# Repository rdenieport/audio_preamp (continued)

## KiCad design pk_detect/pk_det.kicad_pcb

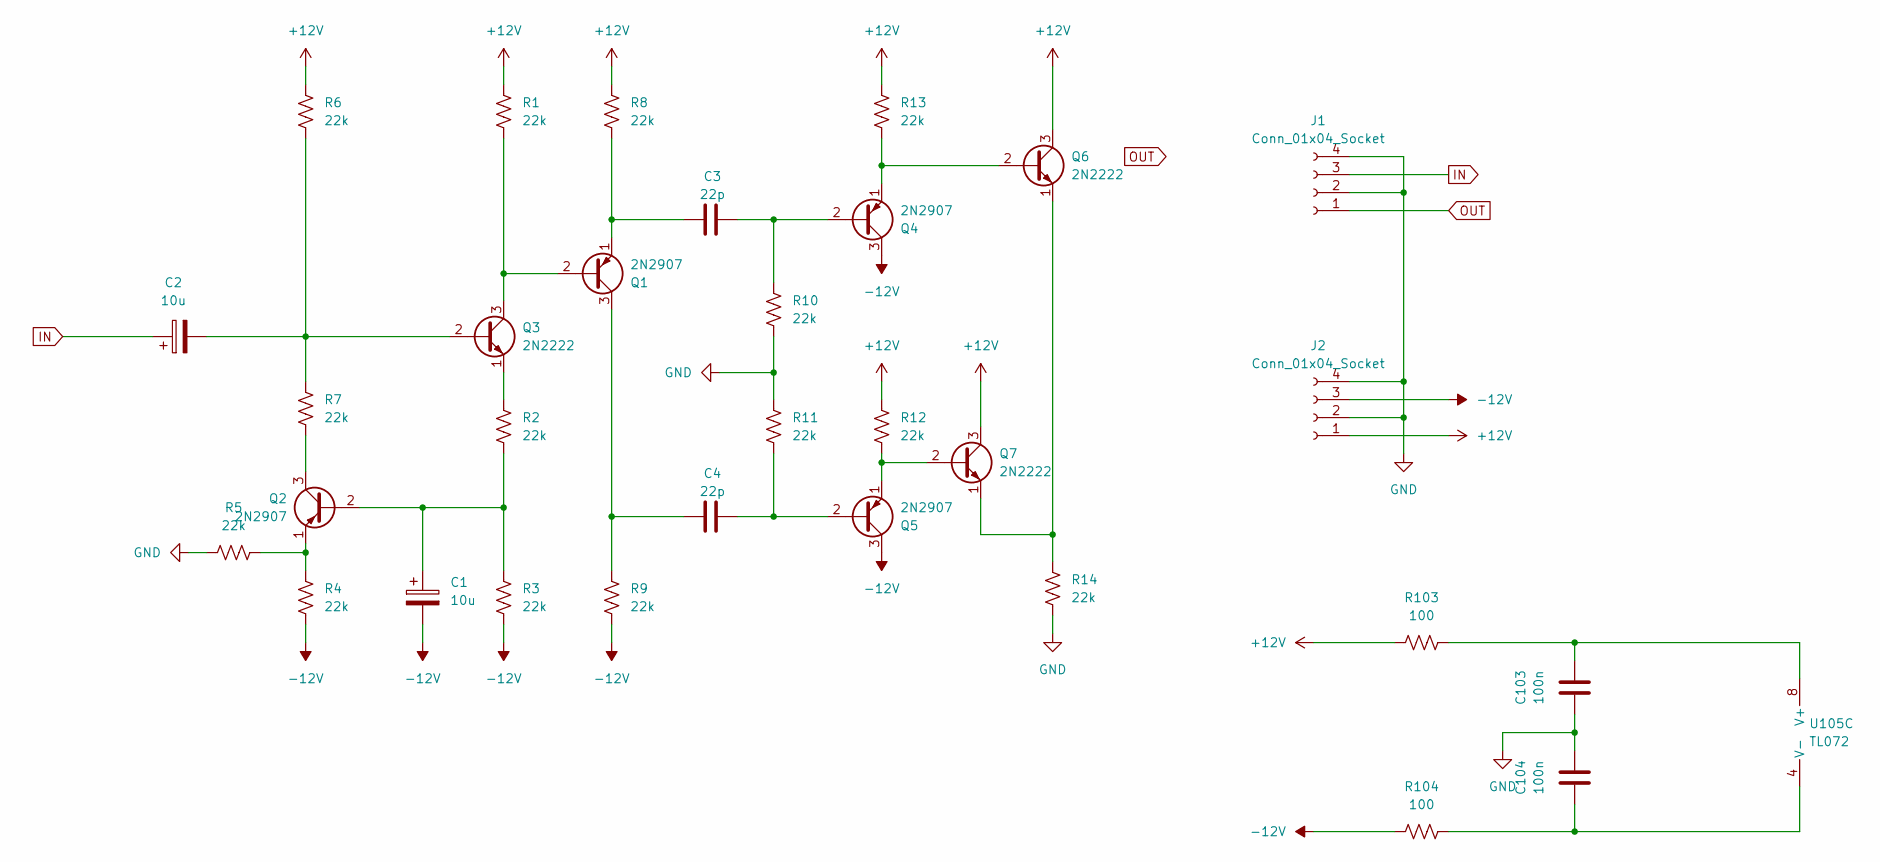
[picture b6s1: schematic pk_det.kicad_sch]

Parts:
C1, C2: 10u; CP_Radial_D6.3mm_P2.50mm
C3, C4: 22p; C_Disc_D4.3mm_W1.9mm_P5.00mm
C103, C104: 100n; C_Disc_D4.3mm_W1.9mm_P5.00mm
J1, J2: Conn_01x04_Socket; Molex_KK-254_AE-6410-04A_1x04_P2.54mm_Vertical
Q1, Q2, Q4, Q5: 2N2907; TO-46-3
Q3, Q6, Q7: 2N2222; TO-46-3
R1, R2, R3, R4, R5, R6, R7, R8, R9, R10, R11, R12, R13, R14: 22k; R_Axial_DIN0207_L6.3mm_D2.5mm_P10.16mm_Horizontal
R103, R104: 100; R_Axial_DIN0207_L6.3mm_D2.5mm_P10.16mm_Horizontal
U105: TL072; DIP-8_W7.62mm_LongPads

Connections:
+12V: J2.1, Q6.3 (C), Q7.3 (C), R1.1, R6.1, R8.1, R12.1, R13.1, R103.1
-12V: C1.2, J2.3, Q4.3 (C), Q5.3 (C), R3.2, R4.2, R9.2, R104.1
GND: C103.1, C104.2, J1.2, J1.4, J2.2, J2.4, R5.2, R10.2, R11.1, R14.2
IN: C2.1, J1.3
unnamed: Q1.2 (B), Q3.3 (C), R1.2
unnamed: C4.1, Q1.3 (C), R9.1
unnamed: C3.1, Q1.1 (E), R8.2
unnamed: C1.1, Q2.2 (B), R2.2, R3.1
unnamed: Q2.3 (C), R7.2
unnamed: Q2.1 (E), R4.1, R5.1
unnamed: C2.2, Q3.2 (B), R6.2, R7.1
unnamed: Q3.1 (E), R2.1
unnamed: C3.2, Q4.2 (B), R10.1
unnamed: Q4.1 (E), Q6.2 (B), R13.2
unnamed: C4.2, Q5.2 (B), R11.2
unnamed: Q5.1 (E), Q7.2 (B), R12.2
unnamed: Q6.1 (E), Q7.1 (E), R14.1
unnamed: C103.2, R103.2, U105.8 (V+)
unnamed: C104.1, R104.2, U105.4 (V-)
OUT: J1.1

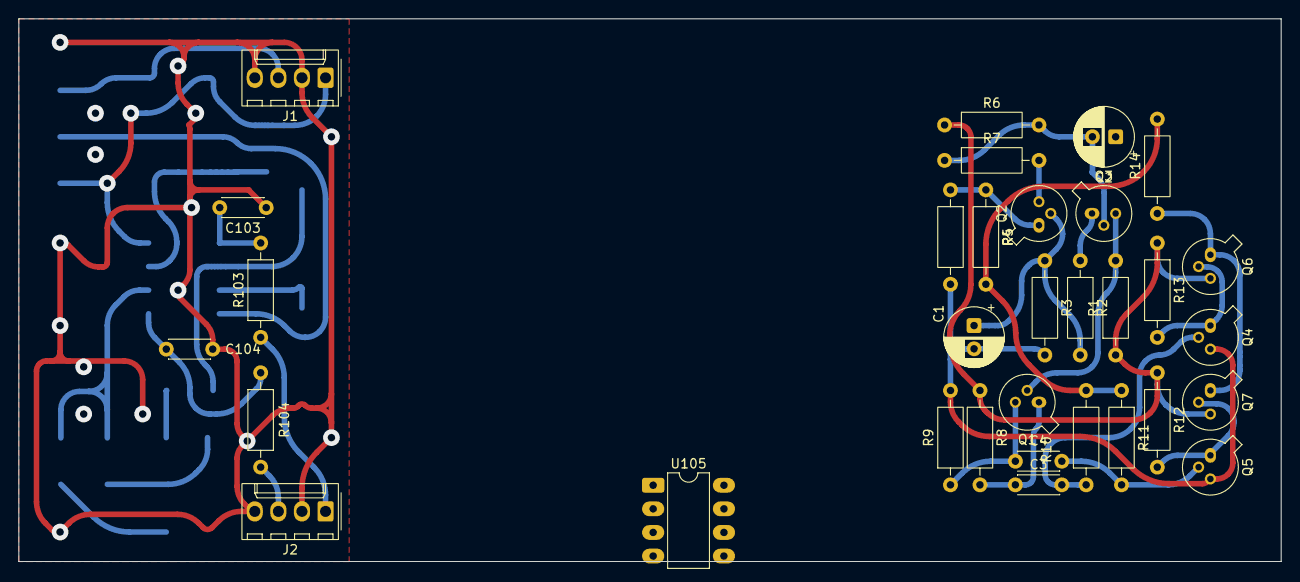
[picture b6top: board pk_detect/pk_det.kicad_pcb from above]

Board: 2 copper layers, 135.9 x 58.4 mm, 32 parts (0 on the bottom side), 19 nets.

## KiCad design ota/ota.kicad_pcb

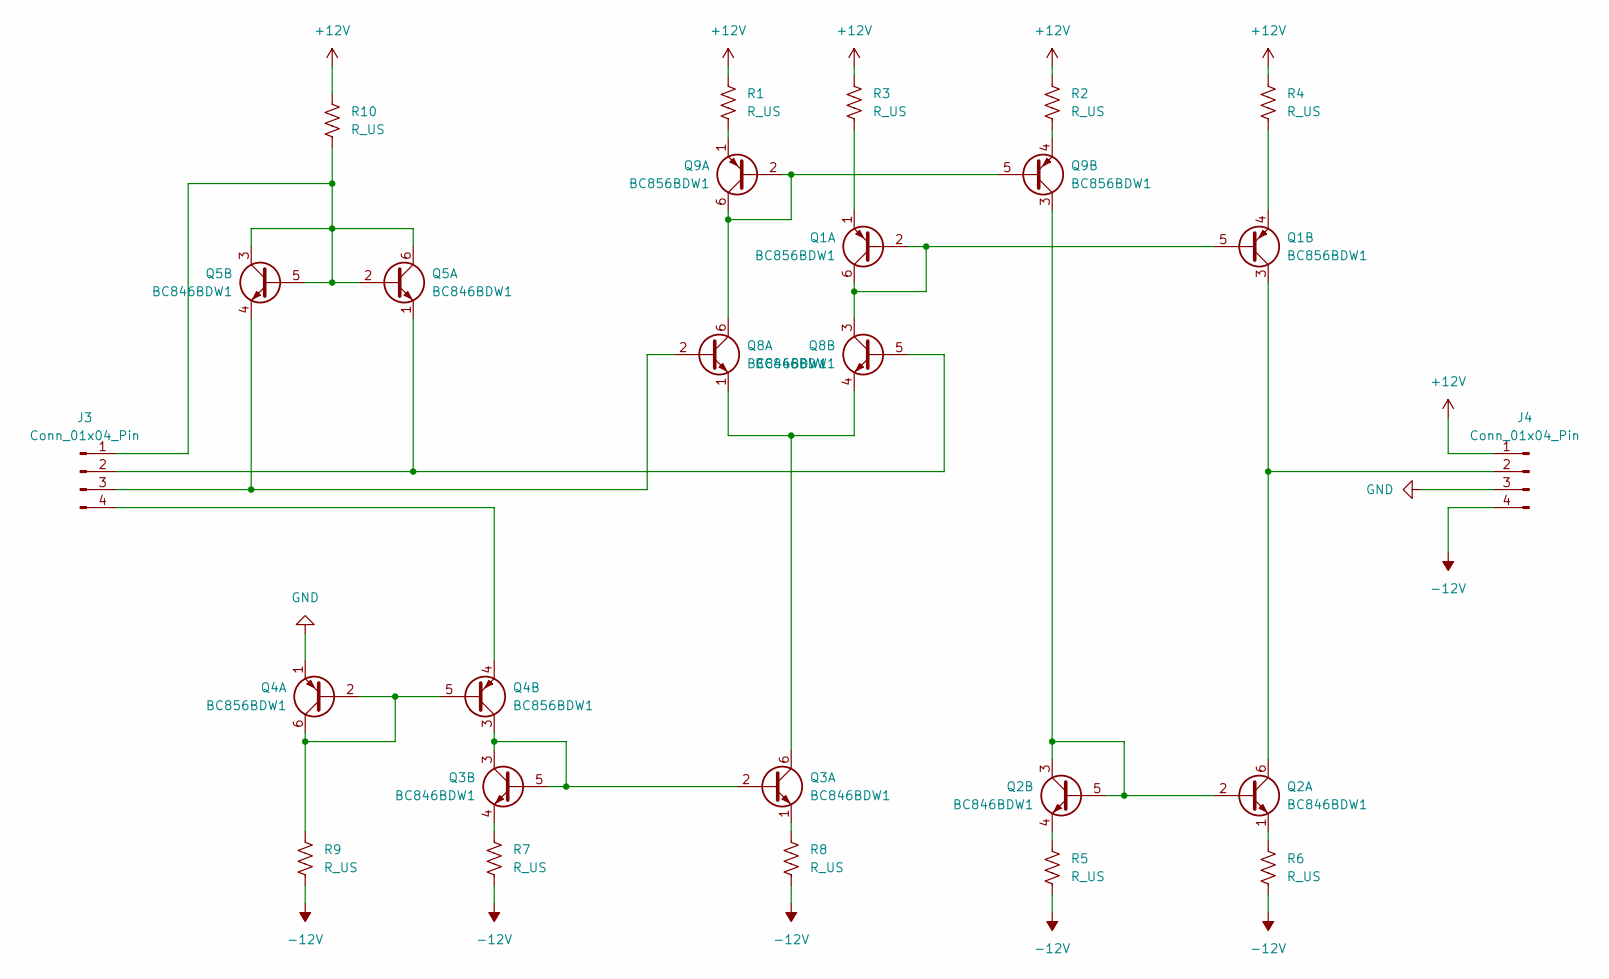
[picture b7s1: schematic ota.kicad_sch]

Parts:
J3, J4: Conn_01x04_Pin; PinHeader_1x04_P2.54mm_Vertical
Q1, Q4, Q9: BC856BDW1; SOT-363_SC-70-6
Q2, Q3, Q5, Q8: BC846BDW1; SOT-363_SC-70-6
R1, R2, R3, R4, R5, R6, R7, R8, R9, R10: R_US; R_0402_1005Metric_Pad0.72x0.64mm_HandSolder

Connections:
+12V: J4.1, R1.1, R2.1, R3.1, R4.1, R10.1
-12V: J4.4, R5.2, R6.2, R7.2, R8.2, R9.2
GND: J4.3, Q4.1 (E1)
unnamed: J3.1, Q5.2 (B1), Q5.3 (C2), Q5.5 (B2), Q5.6 (C1), R10.2
unnamed: J3.2, Q5.1 (E1), Q8.5 (B2)
unnamed: J3.3, Q5.4 (E2), Q8.2 (B1)
unnamed: J3.4, Q4.4 (E2)
unnamed: J4.2, Q1.3 (C2), Q2.6 (C1)
unnamed: Q1.2 (B1), Q1.5 (B2), Q1.6 (C1), Q8.3 (C2)
unnamed: Q1.1 (E1), R3.2
unnamed: Q1.4 (E2), R4.2
unnamed: Q2.2 (B1), Q2.3 (C2), Q2.5 (B2), Q9.3 (C2)
unnamed: Q2.1 (E1), R6.1
unnamed: Q2.4 (E2), R5.1
unnamed: Q3.2 (B1), Q3.3 (C2), Q3.5 (B2), Q4.3 (C2)
unnamed: Q3.6 (C1), Q8.1 (E1), Q8.4 (E2)
unnamed: Q3.1 (E1), R8.1
unnamed: Q3.4 (E2), R7.1
unnamed: Q4.2 (B1), Q4.5 (B2), Q4.6 (C1), R9.1
unnamed: Q8.6 (C1), Q9.2 (B1), Q9.5 (B2), Q9.6 (C1)
unnamed: Q9.1 (E1), R1.2
unnamed: Q9.4 (E2), R2.2

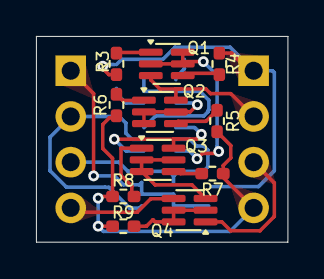
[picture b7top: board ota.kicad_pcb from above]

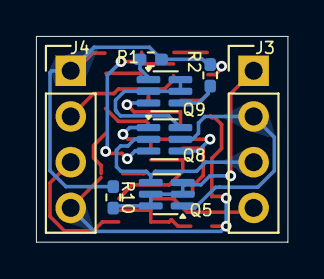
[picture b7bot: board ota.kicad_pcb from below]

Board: 2 copper layers, 14.0 x 11.4 mm, 19 parts (8 on the bottom side), 22 nets.

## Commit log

2025-03-19 before breaking everything
2025-03-19 Done
2025-03-19 gitignore
2025-03-24 vumeter
2026-04-16 before changing med
2026-04-16 med ok
2026-04-16 lf/hf ok
2026-04-20 change arch
